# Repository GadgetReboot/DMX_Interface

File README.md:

# DMX_Interface
DMX  RS485 to TTL isolated interface
<br><br><BR><BR>
The XLR connectors used in the prototype are from Ali Express with part numbers C1019 and C1020 but it can be awkward to search for it on there.   Using a search engine and searching for "C1019 C1020 XLR 3 pin"  may show some Ali Express results that work better than searching directly on the site.

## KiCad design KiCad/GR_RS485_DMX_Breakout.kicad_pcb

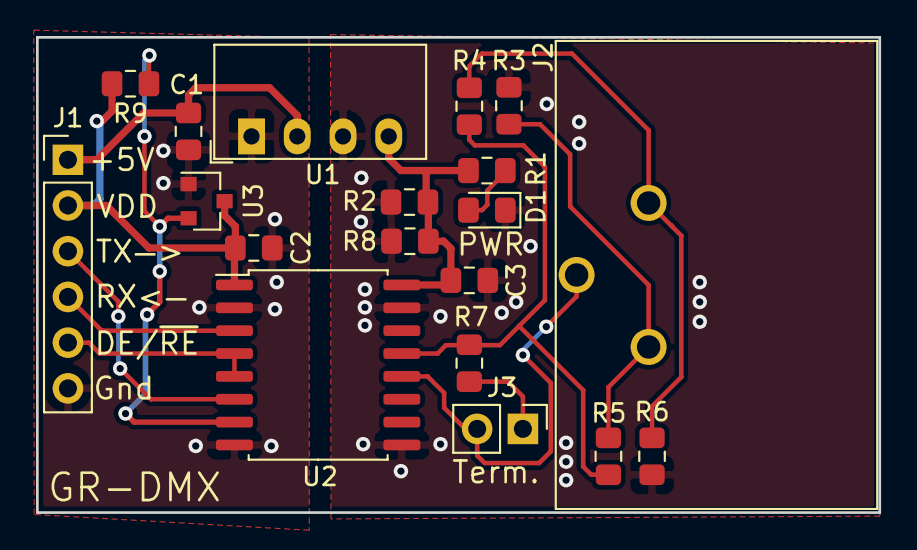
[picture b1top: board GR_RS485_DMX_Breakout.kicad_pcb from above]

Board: 2 copper layers, 46.8 x 26.4 mm, 19 parts (0 on the bottom side), 15 nets.

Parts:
C1, C2, C3: 100nF; C_0805_2012Metric_Pad1.15x1.40mm_HandSolder
D1: LED_Small_ALT; LED_0805_2012Metric_Pad1.15x1.40mm_HandSolder
J1: Conn_01x06; PinHeader_1x06_P2.54mm_Vertical
J2: XLR3; DIN3_XLR
J3: Conn_01x02; PinHeader_1x02_P2.54mm_Vertical
R1: 1K; R_0805_2012Metric_Pad1.15x1.40mm_HandSolder
R2, R8: 510r; R_0805_2012Metric_Pad1.15x1.40mm_HandSolder
R3, R4: DNI; R_0805_2012Metric_Pad1.15x1.40mm_HandSolder
R5, R6: 0r; R_0805_2012Metric_Pad1.15x1.40mm_HandSolder
R7: 120r; R_0805_2012Metric_Pad1.15x1.40mm_HandSolder
R9: 10K; R_0805_2012Metric_Pad1.15x1.40mm_HandSolder
U1: CRE1S0505SC; Converter_DCDC_muRata_CRE1xxxxxxSC_THT
U2: ADM2483xRW; SOIC-16W_7.5x10.3mm_P1.27mm
U3: ADM809; SOT-23

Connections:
+5V: C1.1, J1.1, U1.2
GND: C3.1, D1.1, R2.2, R3.2, R6.1, R8.2, U1.3, U2.9, U2.15
GNDREF: C1.2, C2.2, J1.6, U1.1, U2.2, U2.8, U3.1
unnamed: D1.2, R1.2
unnamed: J1.3, U2.6
unnamed: J1.4, U2.3
unnamed: J1.5, U2.4, U2.5
unnamed: J2.1, R4.2, R6.2
unnamed: J2.2, R3.1, R5.1
unnamed: J2.3, J3.2, U2.12
unnamed: J3.1, R7.1
unnamed: R4.1, R5.2, R7.2, U2.13
unnamed: R9.1, U2.7, U3.2
VCC: C3.2, R1.1, R2.1, R8.1, U1.4, U2.16
VDD: C2.1, J1.2, R9.2, U2.1, U3.3
